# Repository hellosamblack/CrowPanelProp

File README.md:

# Communicator / Scanner Prop Firmware

Cassette-futurism communicator/scanner prop for the **CrowPanel Advance ESP32-P4 (hardware V1.0)**.
Custom ESP-IDF firmware structured as a generic *prop engine*: stable firmware whose behavior is driven
live over WiFi, so scenes/LEDs/screen text can be cued and iterated without reflashing.

Forked from `example/V1.0/idf-code/Lesson09-LVGL_Lighting_Control`.

## Architecture

| Module | Role |
|--------|------|
| `components/bsp_display`, `bsp_illuminate`, `bsp_i2c` | Display + touch + backlight bring-up (reused from Lesson09) |
| `components/bsp_io` | Discrete on/off LEDs + debounced buttons (`espressif/button`) |
| `main/prop_engine` | **The brain.** Scene state machine + 10 Hz animation task; single source of truth, fans state out to observers |
| `main/prop_net` | WiFi **AP+STA** via the onboard ESP32-C6 (`esp_hosted`); STA credentials in NVS |
| `main/prop_api` | HTTP server: operator web console, REST `/cmd`, WebSocket `/ws`, OTA `/ota` |
| `main/prop_ui` | LVGL amber-on-black retro readout — a pure view of engine state |

Inputs (physical buttons, remote commands) all funnel through `prop_engine`, which drives both the LEDs
and the screen, so they never drift out of sync.

## Scenes

`IDLE`, `SCANNING`, `SIGNAL_ACQUIRED`, `COMMS`, `ALERT` — each defines status text + an animated LED pattern.

## Build & flash

Requires **ESP-IDF ≥ 5.4.2** (v6.0.1 recommended).

**Windows:**
Use the VS Code ESP-IDF extension terminal, or `export.ps1` from your IDF install:
```powershell
idf.py set-target esp32p4
idf.py build
idf.py -p <PORT> flash monitor     # first flash over USB (UART0)
```
Or run the helper: `pwsh tools/dev.ps1 bf -Port COM7`

**Linux / Debian:**
Source your `export.sh` script to activate the environment:
```bash
. ~/.local/esp/esp-idf/export.sh
idf.py set-target esp32p4
idf.py build
idf.py -p /dev/ttyUSB0 flash monitor
```
Or run the helper: `./tools/dev.sh bf -Port /dev/ttyUSB0`

The `espressif/button`, display, and WiFi components download automatically on first build
(declared in the `idf_component.yml` files).

## Live control (no reflash)

Find the device IP from the serial log (or use the AP `PROP-COMMS` / pass `scanner99`, then `192.168.4.1`).

```bash
# REST
curl -X POST http://<ip>/cmd -d '{"cmd":"scene","value":"SCANNING"}'
curl -X POST http://<ip>/cmd -d '{"cmd":"led","name":"alert","on":true}'
curl -X POST http://<ip>/cmd -d '{"cmd":"channel","value":"CH 04 / 147.55 MHz"}'
curl      http://<ip>/state

# Operator cue board (scene buttons, live state): open http://<ip>/ in a browser
# WebSocket: ws://<ip>/ws  — send the same JSON commands, receive state broadcasts
```

Command schema: see the top of [main/include/prop_api.h](main/include/prop_api.h).

### WiFi OTA (code changes, still no USB)

**CLI (recommended)** — build + push in one command:

**Windows (PowerShell):**
```powershell
pwsh tools/dev.ps1 ota                          # defaults to comm-unit-7.local
pwsh tools/dev.ps1 ota -DeviceHost 172.17.2.167 # explicit IP fallback
```

**Linux / Debian (Bash):**
```bash
./tools/dev.sh ota                              # defaults to comm-unit-7.local
./tools/dev.sh ota -DeviceHost 172.17.2.167     # explicit IP fallback
```

**Browser** — open `http://comm-unit-7.local/`, scroll to **FIRMWARE UPDATE**, pick the
`.bin` (usually `build/communicator.bin`), click **UPLOAD**. A progress percentage appears
and the page reports "done — rebooting…" when the device is switching over.

**Raw curl** (if you prefer):

```bash
idf.py build
curl -X POST "http://<ip>/ota?token=prop-ota-2024" --data-binary @build/communicator.bin
```

**Rollback safety:** the bootloader is configured with `CONFIG_BOOTLOADER_APP_ROLLBACK_ENABLE`.
A freshly-OTA'd image boots as `PENDING_VERIFY`; `app_main` calls
`esp_ota_mark_app_valid_cancel_rollback()` after the full stack is up. If the new image
crashes before reaching that point the bootloader automatically reverts to the previous
partition on the next reset — no USB reflash required.

**Confirm the update landed:** `GET /state` includes a `"version"` field (from `git
describe`), and the web console state line shows `v<version>`.

Change `PROP_OTA_TOKEN` in [main/include/prop_api.h](main/include/prop_api.h) and the AP password in
[main/include/prop_net.h](main/include/prop_net.h) before any real deployment.

## Wiring — IMPORTANT

GPIO assignments are placeholders in [components/bsp_io/bsp_io.c](components/bsp_io/bsp_io.c). Only **GPIO48**
(the UART1-RX header pin) is confirmed broken-out and free. **Verify every other pin against the V1.0
schematic in `Eagle_SCH&PCB/1.0/` and the connector silkscreen before wiring.** Defaults used:

- LEDs: `power`=GPIO48, `signal`=GPIO47 (UART1-TX), `alert`=GPIO20
- Buttons (active-low, internal pull-up): `mode`=GPIO33 (UART3-IN), `action`=GPIO11

Buttons: `mode` cycles scenes, `action` jumps to SCANNING (edit `on_button()` in `main/main.c`).

## ESP-IDF version

**Builds clean on ESP-IDF v6.0.1** (target esp32p4). The Lesson09/17 examples were written for 5.4.2; this
project was migrated to 6.0. Changes required for 6.0 (all already applied):

- cJSON moved out of IDF core → added `espressif/cjson` dependency; `REQUIRES cjson` (not `json`).
- WiFi stack: `esp_wifi_remote` bumped to **1.x** (0.x referenced the removed `esp_interface.h`); paired with `esp_hosted` 2.12.9.
- `driver` component split → BSP components now require `esp_driver_i2c` / `esp_driver_gpio` / `esp_driver_ledc`.
- esp_lcd DPI API: `lcd_color_rgb_pixel_format_t`→`lcd_color_format_t`, `LCD_COLOR_PIXEL_FORMAT_*`→`LCD_COLOR_FMT_*`, `.pixel_format`→`.in_color_format`/`.out_color_format`, `.flags.use_dma2d` removed, RGB666 enum gone.
- Stricter warnings-as-errors: fixed a header-guard typo in `bsp_i2c.h`.
- `sdkconfig.defaults`: 16 MB flash + `CONFIG_LV_FONT_MONTSERRAT_24`.

## Status

**Compiles successfully** (`communicator.bin` builds). **Not yet flashed/run on hardware** — pending the
CH341 USB-serial driver + the board appearing on a COM port. Then work through the verification checklist
in the project plan.

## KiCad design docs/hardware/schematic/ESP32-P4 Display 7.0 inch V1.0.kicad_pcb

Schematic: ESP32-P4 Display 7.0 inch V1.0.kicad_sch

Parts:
C1, C2, C3, C10, C17, C22, C69, C86, C102: 1uF; 0603
C4: 10uF/NC; 0603
C5, C7, C9, C36, C40, C41, C43, C45, C46, C50, C60, C61, C63, C72, C73, C108, C113, C115: 100nF; C0402
C6, C8, C42, C44, C47, C48, C49, C56, C71, C107, C112, C114, C116: 10uF; C0402
C11, C15, C19, C20, C21, C35, C37, C52, C53, C54, C75, C76, C77, C80, C81, C82, C84, C144, C150, C151, C152, C155, C156, C159: 100nF; 0603
C12, C27, C28, C32: 10uF/10V+; 0603
C13, C18: 22uF; C0805
C14, C16, C38, C74, C78, C79, C83, C136, C149, C153, C157: 10uF; 0603
C23, C24, C103, C104: 47uF; 0603
C26, C31: 22pF; 0603
C29, C30: 12pF; C0402
C33, C34: 15pF; C0402
C39, C130, C132, C145: 100nF_NC; C0402
C51, C55, C57, C58, C59, C64, C65, C66: 1uF; C0402
C62: 10nF; C0402
C67, C68, C85, C105, C106, C158: 1nF; 0603
C70: 10UF; 0603
C87: 15pF; 0603
C88: 10UF_NC; 0603
C89, C101: 22pF_NC; C0402
C90, C99, C110: 10uF/25V; 0603
C91, C100, C111: 100nF/50V; 0603
C92: 22uF/16V; C0805
C93: 10nF/25V; 0603
C94: 10uF/25V; C0402
C95: 100nF/50V; C0402
C96, C97: 1uF/25V; 0603
C98, C109: 1uF/50V; 0603
C117, C118, C119, C120, C121, C122, C123, C124, C125, C126, C127, C128, C129, C131, C133, C137, C138, C139, C140, C141, C142, C146: 1uF_NC; C0402
C134, C148: 47uF_NC; 0603
C135, C147, C154: 100nF_NC; 0603
C143: 1uF_NC; 0603
D1: KT-0603RYG; LED_KT-0603RYG
D2, D007, D10: DSS34; D_SOD123FL
D003: NC/DSS34; D_SOD123FL
D4, D008, D11: 1N5817WS; D_SOD323
D005, D012, D013, D015, D017, D018: LMBR140ET1G
D14: Red; LED0603
D016: MM1W18_18V; LMSZ5233BT1G
D020: LMSZ5233BT1G_-6V; LMSZ5233BT1G
FB2, FB3, FB10, FB11: 1K/磁珠; L0603
FB4, FB5, FB13: 0R/800mA_NC; L0402
FB6: 0R/800mA; L0402
FB7, FB8, FB9, FB12: 1K/磁珠_NC; L0603
FB14: 0R/800mA_NC; R0402
FB15, FB16: 0R/800mA_NC; L0603
FB17, FB18, FB19, FB20: 0R/800mA; L0603
FB21: 0R/800mA; L0805
FPC2: FPC-6PIN-0.5MM
FPC3: AFC24-S24FIA-00; FPC-SMD_P0.50-24P_QCHF-SM-H2.0
IC1: ESP32-C6-MINI-1-N4; ESP32C6MINI1N4
IC2: ME6211C18M5G-N; SOT95P282X145-5N
IC3: ME6211C28M5G-N; SOT95P282X145-5N
IC4: ME6211C18M5G-N_NC; SOT95P282X145-5N
IC5: ES7210_NC; QFN40P400X400X80-33N
IC6: ES8311_NC; QFN40P300X300X60-21N
IC7, IC8: ME6211C33M5G-N; SOT95P282X145-5N
IC10: W25Q128JVSIQ; SOIC127P790X216-8N
J1, J16: TYPEC-3.0-16P-SMD; USB-3.0TYPEC-SMD
J2, J13: HY2.0-4P-SMT; CONNECTOR_4P-SMD-2.0
J3, J4, J6: PH2.0WT-2PIN
J5: HOLDER-MICROSD-9P; 9P-SMD-W_-RING
J7: CONN_12X22X12-SMD1; 2X12-SMD1
J8: HC-PZ200-8.7L-1X4PZ1; TEST-PIN-4-2.0MM
J9, J11: HEADER-7P-18.28X2.5; H7-2.54-18.28X2.5X5MM
J10: XH2.54-4P-SMT; XH2.54-4P-SMD
J12, J14, J15, J18: THO-M3.25MM-HOLE; THO-M3.2_5MM-HOLE
J21: C23398852_30P_0.5MM_下接_FC-05A30P11H20
K3, K4: KEY-4.5X4.5; KEY-4.5X4.5-SMD
L1, L6: 2.2μH_C5179446; 1008(2520)
L2, L5: 4.7uH_C45385206_2.4A; 1008(2520)
L4: NC; L0603
P1, P2, P3, P4, P5, P6, P7, P8, P9, P10, P11, P12, P13, P14, P15, P16, P17, P18, P19, P20, P21, P22, P23, P24, P25, P26, P27, P28, P29, P30, P31, P32, P33, P34, P35, P36, P37, P38, P39, P40, P41, P42, P43, P44, P45, P46, P47, P48, P49, P50, P51, P52, P53, P54, P55, P56, P57, P58, P59, P60, P61, P62, P63, P64, P65, P66, P67, P68, P69, P70, P71, P72, P73, P74, P75, P76, P77, P78, P79, P80, P81, P82, P83, P84, P85, P86, P87, P88: TEST_PADPAD-1.5MM; TEST_PAD-1.5MM
Q1, Q2, Q4, Q6, Q7, Q8, Q9: BSS138W_SOT323; MOS_SOT323
Q3, Q5: NCE20P45Q; PDFN3333
Q10: AO3401; PMOS_SOT23
Q11: AO3401_NC; PMOS_SOT23
R1, R5, R9, R15, R18, R27, R28, R29, R30, R53, R54, R61, R66, R67, R71, R77, R87, R91, R106, R116, R160, R180, R181: 10K; R0603
R2, R117, R139, R165: 100K; R0603
R3, R4, R17, R26, R47, R50, R96, R101: 5.1K; R0603
R6, R7, R8, R10, R13, R24, R48, R49, R55, R60, R65, R76, R103, R112, R113, R114, R115, R118, R119, R129, R149, R184, R188, R189: 0R; R0603
R11: 22.1K; R0603
R12, R19, R20, R36, R37, R38, R39, R40, R41, R42, R43, R44, R70, R80, R88, R89, R90, R92, R95, R99, R100, R102, R105, R109, R127, R162, R190, R216, R217, R332: 0R; R0402
R14, R21: NC/499K; R0603
R16, R31, R32: 2K; R0603-SP
R22, R45, R46, R51, R52, R56, R57, R58, R59, R62, R74, R78, R93, R94, R97, R98: 4.7K; R0603
R23: 0R; C0402
R25: 0R; R0603-SP
R33: 10K_NC; R0603
R35: NC/10M; R0402
R63, R64, R68, R108, R122, R123: 100K; R0402
R65_NC0, R131, R171: 10K; R0402
R69: 4.7K; R0603-SP
R72, R73: 10K_NC; R0402
R75: 4.7K_NC; R0603
R79, R147, R185: OR_NC; R0603-SP
R81, R82, R83, R84, R85, R86, R173, R175: 51K; R0603
R104, R158: 4.02K; R0402
R107, R110, R111, R124, R125, R126, R128, R130, R146, R148, R161, R170, R177: 0R_NC; R0402
R120, R121: 5.1K_NC; R0603
R132, R134: OR; R0402
R141, R142, R144, R145: OR_NC; R0402
R143: 51K; R0603-SP
R152, R153, R154, R155, R156, R157: 100R; R0402
R159: 1.1R; R0603-SP
R163: NC; R0603-SP
R164: 39k; R0603
R166: 180K; R0603
R167: 12K; R0603
R168: 1.91K; R0402
R169: 1K; R0402
R172, R174: 220R; R0603
R178, R179: 20K_NC; R0603
R182: 0R; L0805
R186: 100k; R0603
R187: 10k; R0603
R210: NC/10K; R0603
SW1: switch_6pin; SWITCH_6PIN_2P
TP1, TP2, TP3, TP4, TP5, TP6, TP7, TP8, TP9, TP10, TP11, TP12: TPTP08R; TP08R
U1: CH340K; ESOP-10-EP-150MIL
U2: TP4059-SOT23-6; SOT23-6L
U3, U13: NS4168; NS4168-ESOP-8
U4: NS4263B; SOP16
U6: MT9201; COOPER_SOT23-6
U7: ESP32-P4NRW32; IC_ESP32-P4NRW32
U8: UMH3NTN; SOP65P210X100-6N
U9, U10: MT3406_C22462728; SOT95P280X145-5N
U14: STC8H1K08-36I; TSSOP20
U16: MT3608; SOT95P280X145-6N
U176: LMA3526B381; MIC-SMD_5P-L3.5-W2.7-P1.67
Y2: 40MHZ; X322540MPB4SI
Y3: 24Mhz; 24MHZ_1631-24003-BTKEYA
Y4: 32.768K; NORDIC_NRF_XTAL_3215_N

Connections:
3V3$: C2.2, U1.10 (V3)
13: R189.2, U14.3 (MISO/P1.4)
14: R188.2, U14.4 (SCLK/P1.5)
+5V_IN: D2.+, D4.+, J10.3, P66.P$1, R46.1, R51.1
+VBUS1: D10.+, D11.+, J1.A4, J1.A9, J1.B4, J1.B9, P1.P$1
+VBUS2: D007.+, D008.+, J16.A4, J16.A9, J16.B4, J16.B9, P87.P$1
ADC_AVDD_3V3: C132.1, C133.2, FB5.2, IC5.22 (VDDA), IC5.23 (VDDM)
ADC_DVDD_3V3: C130.1, C131.2, FB4.2, IC5.6 (VDDP), IC5.7 (VDDD), R73.1
ADC_VBAT: C158.2, R164.2, R186.1, U14.13 (P3.2/ADC10)
AGND: C102.2, C103.2, C104.2, C105.1, C106.1, C134.1, C143.1, C148.1, C154.2, FB19.2, FB21.2, J4.P$3, J4.P$4, R79.2, R143.1, R185.1, U4.2, U4.7, U4.15, U13.7 (GND), U13.9 (PE)
AGND1: C72.1, C117.1, C118.1, C119.1, C120.1, C121.1, C122.1, C127.2, C128.2, C129.2, C132.2, C133.1, C137.1, C138.2, C139.2, C142.2, C145.2, C146.1, IC5.21 (GNDA), IC6.10 (AGND), R144.1, R145.2, R171.2, R182.2, U176.5_1 (5), U176.5_2 (5)
AGND3: C22.2, C23.2, C24.2, C67.1, C68.1, FB20.2, J6.P$3, J6.P$4, U3.7 (GND), U3.9 (PE)
AUDIO_CTRL: Q10.3 (D), R117.2, R139.2
AUDIO_OUT_5V: C134.2, C148.2, C154.1, FB15.2, U4.4, U4.13
AUDIO_OUT_SD: Q10.1 (G), R71.1, R147.1, U7.60 (GPIO30)
AUDIO_VDD1: C102.1, C103.1, C104.1, FB17.1, U13.6 (VDD)
AUDIO_VDD2: C22.1, C23.1, C24.1, FB18.1, U3.6 (VDD)
AUDIO_VDD_3V3: C152.2, C153.2, FB4.1, FB5.1, FB6.1, FB14.1, FB16.2, IC7.5 (VOUT)
AVDD_2V8: C82.2, C83.2, FPC3.1, FPC3.2, IC3.5 (VOUT), P83.P$1
C6_EN: C15.1, IC1.8 (EN), R77.1, U7.63 (GPIO32)
C6_IO8: IC1.22 (IO8), R87.2
C6_IO9_BOOT: IC1.23 (IO9), P36.P$1
C6_RXD0: IC1.30 (RXD0), P21.P$1
C6_TXD0: IC1.31 (TXD0), P25.P$1
C6_VDD_3V3: C11.1, C14.2, IC1.3 (3V3), P37.P$1, R76.1, R77.2, R81.1, R82.1, R83.1, R84.1, R85.1, R86.1, R87.1
CODEC_3V3: C145.1, C146.2, FB13.2, FB14.2, IC6.3 (PVDD), IC6.4 (DVDD)
CSID0_P: R153.1, U7.43 (CSI_DATAP0)
CSI_CLK_N: FPC3.19, R156.2, TP5.TP
CSI_CLK_P: FPC3.18, R157.2, TP6.TP
CSI_D0_N: FPC3.16, R152.2, TP1.TP
CSI_D0_P: FPC3.15, R153.2, TP2.TP
CSI_D1_N: FPC3.22, R154.2, TP3.TP
CSI_D1_P: FPC3.21, R155.2, TP4.TP
CSI_RESET: FPC3.8, P80.P$1, Q4.2 (S), R57.2
CSI_SCL: FPC3.4, P81.P$1, Q7.2 (S), R62.2
CSI_SDA: FPC3.5, P82.P$1, Q6.2 (S), R56.2
DA1: J5.8 (DATA1), P56.P$1, R15.1
DA2: J5.1 (DATA2), P53.P$1, R30.1
DOVDD_1V8: C77.2, C78.2, C84.2, C85.2, FPC3.9, IC2.5 (VOUT), P84.P$1, Q4.1 (G), Q6.1 (G), Q7.1 (G), R56.1, R57.1, R62.1, R67.2, Y3.4 (4_VDD)
DOWNLOAD_BOOT: R60.1, R106.2
DSI_CLK_N: J21.18, R100.1, TP11.TP
DSI_CLK_P: J21.17, R102.1, TP12.TP
DSI_DATA0_N: J21.24, R190.1, TP7.TP
DSI_DATA0_P: J21.23, R92.1, TP8.TP
DSI_DATA1_N: J21.21, R95.1, TP9.TP
DSI_DATA1_P: J21.20, R99.1, TP10.TP
DTR: R5.2, U1.4 (DTR#), U8.4 (E2)
EN_DCDC: R13.2, U7.79 (EN_DCDC)
ESP32_LDO1: C58.1, R105.2, U7.71 (VFB1/VO1)
ESP32_LDO2: C57.1, R40.2, U7.72 (VFB2/VO2)
ESP32_LDO3: C59.1, R80.2, U7.73 (VFB3/VO3)
ESP32_LDO4: C66.1, R109.2, U7.74 (VFB4/VO4)
FB_DCDC: C31.1, R14.2, R21.1, R103.1, U10.5 (FB)
FLASH_CK: IC10.6 (CLK), U7.32 (FLASH_CK)
FLASH_CS: IC10.1 (/CS), R65_NC0.1, U7.27 (FLASH_CS)
FLASH_D: IC10.5 (DI_(IO0)), U7.33 (FLASH_D)
FLASH_HOLD: IC10.7 (/HOLD_OR_/RESET_(IO3)), U7.31 (FLASH_HOLD)
FLASH_Q: IC10.2 (DO_(IO1)), U7.28 (FLASH_Q)
FLASH_WP: IC10.3 (/WP_(IO2)), U7.29 (FLASH_WP)
GND: C1.1, C2.1, C3.1, C4.1, C5.2, C6.1, C7.2, C8.1, C9.2, C10.1, C11.2, C12.2, C13.2, C14.1, C15.2, C16.1, C17.1, C18.2, C19.2, C20.1, C21.1, C27.1, C28.2, C29.2, C30.2, C32.1, C33.2, C34.1, C35.1, C36.2, C37.1, C38.1, C39.2, C40.2, C41.2, C42.1, C43.2, C44.1, C45.2, C46.2, C47.1, C48.1, C49.1, C50.2, C51.2, C52.1, C53.1, C54.1, C55.2, C56.1, C57.2, C58.2, C59.2, C60.2, C61.2, C62.2, C63.2, C64.2, C65.2, C66.2, C69.1, C70.2, C71.1, C73.2, C74.1, C75.1, C76.1, C77.1, C78.1, C79.1, C80.1, C81.1, C82.1, C83.1, C84.1, C85.1, C86.1, C87.1, C88.2, C90.2, C91.2, C92.2, C94.2, C95.2, C98.2, C99.2, C100.2, C107.1, C108.2, C109.2, C110.2, C111.2, C112.1, C113.2, C114.1, C115.2, C116.1, C130.2, C131.1, C136.1, C144.1, C149.1, C150.1, C151.1, C152.1, C153.1, C155.1, C156.1, C157.1, C158.1, C159.1, D14.-, D016.2, D018.1, D020.1, FB19.1, FB20.1, FB21.1, FPC2.4, FPC2.7, FPC2.8, FPC3.3, FPC3.6, FPC3.10, FPC3.12, FPC3.17, FPC3.20, FPC3.25, FPC3.26, IC1.1 (GND_1), IC1.2 (GND_2), IC1.11 (GND_3), IC1.14 (GND_4), IC1.36 (GND_5), IC1.37 (GND_6), IC1.38 (GND_7), IC1.39 (GND_8), IC1.40 (GND_9), IC1.41 (GND_10), IC1.42 (GND_11), IC1.43 (GND_12), IC1.44 (GND_13), IC1.45 (GND_14), IC1.46 (GND_15), IC1.47 (GND_16), IC1.48 (GND_17), IC1.49 (GND_18), IC1.50 (GND_19), IC1.51 (GND_20), IC1.52 (GND_21), IC1.53 (GND_22), IC1.54 (GND_23), IC1.55 (GND_24), IC1.56 (GND_25), IC1.57 (GND_26), IC1.58 (GND_27), IC1.59 (GND_28), IC1.60 (GND_29), IC1.61 (GND_30), IC2.2 (VSS), IC3.2 (VSS), IC4.2 (VSS), IC5.8 (GNDD), IC5.33 (EP), IC6.5 (DGND), IC6.20 (CE), IC6.21 (EP), IC7.2 (VSS), IC8.2 (VSS), IC10.4 (GND), J1.A1, J1.A12, J1.B1, J1.B12, J1.P$1, J1.P$2, J1.P$3, J1.P$4, J2.4, J2.SS1, J2.SS2, J3.P$2, J3.P$3, J3.P$4, J5.6 (VSS), J5.G1, J5.G2, J5.G3, J5.G4, J7.7, J7.8, J7.10, J7.21, J7.22, J7.23, J7.24, J8.4, J9.6, J9.6-6 (6), J10.4, J10.5 (SS1), J10.6 (SS2), J12.P$1, J13.4, J13.SS1, J13.SS2, J14.P$1, J15.P$1, J16.A1, J16.A12, J16.B1, J16.B12, J16.P$1, J16.P$2, J16.P$3, J16.P$4, J18.P$1, J21.10, J21.13, J21.16, J21.19, J21.22, J21.25, J21.31, J21.32, K3.1, K4.1, P4.P$1, P10.P$1, P12.P$1, P28.P$1, P31.P$1, P52.P$1, P60.P$1, P65.P$1, P78.P$1, P86.P$1, P88.P$1, R3.1, R4.2, R11.2, R16.1, R18.1, R21.2, R33.2, R64.1, R72.1, R96.1, R101.2, R104.1, R108.1, R123.1, R158.2, R159.1, R160.2, R163.1, R167.1, R169.1, R173.1, R175.1, R182.1, R186.2, SW1.1 (1_2B), SW1.6 (6_1B), U1.3 (GND), U1.EP, U2.2 (GND), U6.2 (2-GND), U7.105 (GND), U9.2 (GND), U10.2 (GND), U14.10 (GND), U16.2 (2_GND), Y2.2 (GND_1), Y2.4 (GND_2), Y3.2 (2_GND)
I2C1_SCL: FPC2.1, P72.P$1, Q9.2 (S), R97.2, U7.88 (GPIO46)
I2C1_SCL_3V3: IC6.1 (CCLK), J11.2, J11.2-2 (2), J13.1, P62.P$1, Q9.3 (D), R93.2, R125.1, R188.1
I2C1_SDA: FPC2.2, P71.P$1, Q8.2 (S), R98.2, U7.87 (GPIO45)
I2C1_SDA_3V3: IC6.19 (CDATA), J11.3, J11.3-3 (3), J13.2, P61.P$1, Q8.3 (D), R94.2, R124.1, R189.1
I2C2_SCL: Q7.3 (D), R59.2, U7.14 (GPIO13)
I2C2_SDA: Q6.3 (D), R22.2, U7.13 (GPIO12)
I2SOUT_LRCK1: R149.2, U13.2 (LRCLK)
I2SOUT_LRCK2: P35.P$1, R114.2, U3.2 (LRCLK)
I2SOUT_SCLK1: R129.2, U13.3 (BCLK)
I2SOUT_SCLK2: P34.P$1, R113.2, U3.3 (BCLK)
I2SOUT_SD1: R112.2, U13.4 (SDATA)
I2SOUT_SD2: P33.P$1, R115.2, U3.4 (SDATA)
I2S_LRCK: R114.1, R130.1, R149.1, U7.23 (GPIO21)
I2S_LRCK_N: IC5.10 (LRCK), IC6.8 (LRCK), R130.2
I2S_MCLK: R126.1, R127.1, U7.52 (GPIO24)
I2S_MCLK_N: IC5.5 (MCLK), IC6.2 (MCLK), R126.2
I2S_SCLK: R113.1, R128.1, R129.1, U7.24 (GPIO22)
I2S_SCLK_N: IC5.9 (SCLK), IC6.6 (SCLK/DMIC_SCL), R128.2
I2S_SDIN1_N: IC5.11 (SDOUT1/TDMOUT)
I2S_SDIN2: R161.1, R162.1, U7.55 (GPIO26)
I2S_SDIN2_N: IC5.12 (SDOUT2/TDMIN), R161.2
I2S_SDOUT: R111.1, R112.1, R115.1, U7.25 (GPIO23)
I2S_SDOUT_N: IC6.9 (DSDIN), R111.2
INLN: C147.1, R148.2
INLN1: R179.1, U4.6
INRN: C135.1, R146.2
INRN1: R178.1, U4.11
INT_TP: FPC2.3, P70.P$1, R75.2, U7.83 (GPIO42)
IO8: R217.1, U7.8 (GPIO8)
IO9_W: J11.5, J11.5-5 (5), P23.P$1, U7.10 (GPIO9)
IO10_W_BUSY: J11.6, J11.6-6 (6), P22.P$1, U7.11 (GPIO10)
IO11_CSI_RESET: Q4.3 (D), R58.2, U7.12 (GPIO11)
LCD_AVDD_9V6: C92.1, C93.1, D005.2, D013.1, J21.9, P19.P$1, R166.2, R168.2
LCD_BK_EN: R160.1, U6.4 (4-EN), U7.61 (GPIO31)
LCD_BK_POWER: Q11.1 (G), R180.1, U7.58 (GPIO29)
LCD_BK_VDD: C13.1, C17.2, L5.1, Q11.3 (D), R184.2, U6.6 (6-VIN)
LCD_RESET: J21.27, P73.P$1, R69.2, U7.82 (GPIO41)
LCD_VCOM_3V3: C94.1, C95.1, J21.30, P20.P$1, R168.1, R169.2
LCD_VDD: C37.2, C38.2, C52.2, C53.2, FPC2.5, IC4.5 (VOUT), J21.28, J21.29, P69.P$1, R63.2, R65.1, R68.2, R122.2
LCD_VGH_18V: C99.1, C100.1, D016.1, J21.3, P18.P$1, R172.1, R173.2
LCD_VGL_-6V: C110.1, C111.1, D020.2, J21.4, P77.P$1, R174.1, R175.2
LED+: C18.1, C19.1, D003.-, D012.1, P63.P$1, R25.1, U6.5 (5-OV)
LED-: J21.7, J21.8, P64.P$1, R159.2, R163.2, U6.3 (3-FB)
MIC1N: C89.2
MIC1P: C101.2
MIC2N: C125.2, R141.2
MIC2P: C126.2, R142.2
MIC2_1: R132.2, R142.1, U176.1
MIC2_2: R131.1, R141.1, R145.1, R171.1, U176.2
MIC2_3: R134.1, R144.2, U176.3
MIC2_VDD_3V3: C72.2, FB6.2, U176.4
MIC3N: C124.1, R170.2
MIC3P: C123.1, R177.2
MIC_L/R: R131.2, U7.22 (GPIO20)
MIC_MCLK: P27.P$1, R127.2, R134.2
MIC_SD2: P30.P$1, R132.1, R162.2
unnamed: R1.1, U9.1 (EN)
unnamed: L1.1, U9.3 (SW)
unnamed: FB7.1, U4.12
unnamed: FB10.1, U13.8 (VOP)
unnamed: R6.1, U1.1 (UD+)
unnamed: R7.1, U1.2 (UD-)
unnamed: R5.1, U8.2 (B1)
unnamed: R9.1, U8.5 (B2)
unnamed: J1.B5, R3.2
unnamed: R8.2, U1.9 (RXD)
unnamed: R10.2, U1.8 (TXD)
unnamed: R16.2, U2.6 (PRO)
unnamed: C26.1, R2.2, R11.1, U9.5 (FB)
unnamed: L6.1, U10.3 (SW)
unnamed: C151.2, IC7.3 (CE), R181.1
unnamed: R13.1, R210.2, U10.1 (EN)
unnamed: C143.2, U4.10
unnamed: R185.2, U4.8
unnamed: D1.3, R31.1, R121.1
unnamed: D1.4, R32.1, R120.1
unnamed: D14.+, R26.1
unnamed: J21.1, J21.2, R25.2
unnamed: J9.1, J9.1-1 (1), R49.1
unnamed: J11.1, J11.1-1 (1), R48.1
unnamed: FB8.1, U4.14
unnamed: Q5.4 (4_G), R78.1, SW1.2 (2_COM2), SW1.5 (5_COM1)
unnamed: J1.A5, R4.1
unnamed: R79.1, U4.16
unnamed: C28.1, R24.1, R210.1, U10.4 (VIN)
unnamed: R190.2, U7.40 (DSI_DATAN0)
unnamed: R92.2, U7.39 (DSI_DATAP0)
unnamed: C30.1, R35.1, U7.1 (GPIO1), Y4.2
unnamed: C29.1, R35.2, U7.104 (GPIO0), Y4.1
unnamed: R95.2, U7.36 (DSI_DATAN1)
unnamed: R99.2, U7.35 (DSI_DATAP1)
unnamed: R100.2, U7.37 (DSI_CLKN)
unnamed: C147.2, R179.2
unnamed: R102.2, U7.38 (DSI_CLKP)
unnamed: R103.2, U7.78 (FB_DCDC)
unnamed: R104.2, U7.34 (DSI_REXT)
unnamed: C21.2, IC4.3 (CE), R53.1
unnamed: C135.2, R178.2
unnamed: FB2.1, U3.8 (VOP)
unnamed: FB11.1, U13.5 (VON)
unnamed: FB3.1, U3.5 (VON)
unnamed: R117.1, U3.1 (CTRL)
unnamed: R118.2, U14.12 (P3.1/ADC9)
unnamed: R119.2, U14.11 (P3.0/ADC8)
unnamed: R139.1, R143.2, U13.1 (CTRL)
unnamed: IC5.3 (CDATA), R124.2
unnamed: IC5.4 (CCLK), R125.2
unnamed: FB9.1, U4.3
unnamed: C155.2, IC8.3 (CE), R116.1
unnamed: C159.2, R187.2, U14.7 (NRST/PWM6/P5.4)
unnamed: FB12.1, U4.5
unnamed: C124.2, IC5.32 (MIC3N)
unnamed: C89.1, IC5.15 (MIC1N)
unnamed: C101.1, IC5.16 (MIC1P)
unnamed: R332.1, U7.7 (GPIO7)
unnamed: R216.1, U7.6 (GPIO6)
unnamed: R158.1, U7.48 (CSI_REXT)
unnamed: R157.1, U7.44 (CSI_CLKP)
unnamed: R156.1, U7.45 (CSI_CLKN)
unnamed: R155.1, U7.47 (CSI_DATAP1)
unnamed: R154.1, U7.46 (CSI_DATAN1)
unnamed: R152.1, U7.42 (CSI_DATAN0)
unnamed: J16.B5, R96.2
unnamed: J16.A5, R101.1
unnamed: C123.2, IC5.31 (MIC3P)
unnamed: C122.2, IC5.30 (REFQ34)
unnamed: C121.2, IC5.29 (REFP34)
unnamed: C76.2, IC2.3 (CE), R61.1
unnamed: C81.2, IC3.3 (CE), R66.1
unnamed: C86.2, R67.1, Y3.1 (1_EN)
unnamed: C120.2, IC5.28 (MIC4P)
unnamed: C119.2, IC5.27 (MIC4N)
unnamed: C118.2, IC5.26 (MICBIAS34)
unnamed: C117.2, IC5.25 (REFQM)
unnamed: C129.1, IC5.24 (MICBIAS12)
unnamed: C125.1, IC5.20 (MIC2N)
unnamed: C126.1, IC5.19 (MIC2P)
unnamed: C127.1, IC5.18 (REFQ12)
unnamed: C128.1, IC5.17 (REFP12)
unnamed: R147.2, U4.1
unnamed: C97.2, D017.1, D018.2
unnamed: IC5.1 (AD0), R73.2
unnamed: IC5.2 (AD1), R72.2
unnamed: C139.1, IC6.14 (DACVREF)
unnamed: C137.2, IC6.16 (VMID)
unnamed: C138.1, IC6.15 (ADCVREF)
unnamed: C140.1, IC6.13 (OUTN)
unnamed: C141.1, IC6.12 (OUTP)
unnamed: C142.1, FB13.1, IC6.11 (AVDD)
unnamed: D003.+, D012.2, L5.2, U6.1 (1-SW)
unnamed: C96.1, C97.1, D013.2, L2.2, U16.1 (1_SW)
unnamed: R165.2, U16.4 (4_EN)
unnamed: C96.2, D005.1, D015.2
unnamed: C98.1, D015.1, R172.2
unnamed: C140.2, R146.1, R170.1
unnamed: C141.2, R148.1, R177.1
P4_IO2: J7.9, P40.P$1, U7.2 (GPIO2)
P4_IO3: J7.11, P41.P$1, U7.3 (GPIO3)
P4_IO4: J7.13, P42.P$1, U7.4 (GPIO4)
P4_IO5: J7.15, P43.P$1, U7.5 (GPIO5)
P4_IO25: J7.17, P85.P$1, U7.53 (GPIO25)
P4_IO27: J7.19, P44.P$1, U7.56 (GPIO27)
P4_IO28: J7.20, P49.P$1, U7.57 (GPIO28)
P4_IO35: R55.2, U7.66 (GPIO35)
P4_IO36: R60.2, U7.68 (GPIO36)
P4_IO39: R90.2, U7.80 (GPIO39)
P4_IO43: R88.2, U7.84 (GPIO43)
P4_IO44: R89.2, U7.86 (GPIO44)
P4_IO49: J7.18, P48.P$1, U7.92 (GPIO49)
P4_IO50: J7.16, P47.P$1, U7.93 (GPIO50)
P4_IO51: J7.14, P46.P$1, U7.94 (GPIO51)
P4_IO52: J7.12, P45.P$1, U7.95 (GPIO52)
P4_RST_EN: C35.2, K4.2, R54.2, U7.103 (CHIP_PU), U8.6 (C1)
P4_RXD2: P59.P$1, R48.2, U7.98 (GPIO54)
P4_TXD2: P58.P$1, R49.2, U7.97 (GPIO53)
P4_VBAT: C9.1, C42.2, R20.1, U7.102 (VBAT)
POWER_CHRG: R50.1, R120.2, U2.1 (CHG), U14.14 (P3.3/ADC11)
POWER_DONE: R47.1, R121.2, U2.5 (STD), U14.15 (P3.4/ADC11)
POWER_G_LED: R31.2, U14.17 (P3.6/ADC14)
POWER_R_LED: R32.2, U14.16 (P3.5/ADC13)
RESET_TP: FPC2.6, P29.P$1, R74.2, U7.81 (GPIO40)
RTS: R9.2, U1.6 (RTS#), U8.1 (E1)
RXD0: R10.1, U7.70 (GPIO38)
RXD1: J2.1, P39.P$1, U7.90 (GPIO48)
RXD3: Q2.2 (S), R45.2, U7.64 (GPIO33)
SD1_CMD: J5.3 (DI), P8.P$1, R28.1, R89.1
SD1_D0: J5.7 (DO), P6.P$1, R27.1, R90.1
SD1_SCK: J5.5 (SCLK), P7.P$1, R88.1
SD2_CLK: IC1.25 (IO19), R82.2, U7.19 (GPIO18)
SD2_CMD: IC1.24 (IO18), R81.2, U7.20 (GPIO19)
SD2_D0: IC1.26 (IO20), R83.2, U7.15 (GPIO14)
SD2_D1: IC1.27 (IO21), R84.2, U7.16 (GPIO15)
SD2_D2: IC1.28 (IO22), R85.2, U7.17 (GPIO16)
SD2_D3: IC1.29 (IO23), R86.2, U7.18 (GPIO17)
SDCS: J5.2 (CS), P57.P$1, R29.1, R33.1
SHLR: J21.6, P75.P$1, R122.1, R123.2
SPI2_MISO: J9.3, J9.3-3 (3), P15.P$1, R332.2
SPI2_MOSI: J9.4, J9.4-4 (4), P14.P$1, R216.2
SPI2_SCK: J9.2, J9.2-2 (2), P16.P$1, R217.2
SPI_BOOT: C54.2, K3.2, R55.1, R91.2, U8.3 (C2)
STBYB: J21.26, P74.P$1, R63.1, R64.2
STC8_RXD: J8.2, R119.1
STC8_TXD: J8.1, R118.1
STC8_VDD_3V3: C69.2, C156.2, C157.2, IC8.5 (VOUT), J8.3, R187.1, U14.8 (VCC), U14.9 (VREF)
TXD0: R8.1, U7.69 (GPIO37)
TXD1: J2.2, P38.P$1, U7.89 (GPIO47)
TXD3: Q1.2 (S), R52.2, U7.65 (GPIO34)
UART_IN_RXD3: J10.2, P67.P$1, Q2.3 (D), R46.2
UART_IN_TXD3: J10.1, P68.P$1, Q1.3 (D), R51.2
UPDN: J21.5, P76.P$1, R68.1, R108.2
USB1_D+: J1.A6, J1.B6, P2.P$1, R6.2
USB1_D-: J1.A7, J1.B7, P3.P$1, R7.2
USB2_D+: J16.A6, J16.B6, U7.50 (DP)
USB2_D-: J16.A7, J16.B7, U7.49 (DM)
VBAT: C4.2, J3.P$1, P9.P$1, Q3.5 (5_D), Q3.6 (6_D), Q3.7 (7_D), Q3.8 (8_D), Q3.9 (9_D), R17.1, R164.1, U2.3 (BAT)
VCC5V: C136.2, C144.2, D1.1, D1.2, D2.-, D007.-, D10.-, IC8.1 (VIN), P11.P$1, Q3.1 (1_S), Q3.2 (2_S), Q3.3 (3_S), Q5.1 (1_S), Q5.2 (2_S), Q5.3 (3_S), R78.2, R116.2
VCC5V_IN: C3.2, D4.-, D008.-, D11.-, Q3.4 (4_G), R17.2, R18.2, R47.2, R50.2, U2.4 (VCC)
VCCA: C43.1, C47.2, R23.1, U7.51 (VCCA)
VDD5V: C12.1, C90.1, C91.1, C149.2, C150.2, FB15.1, FB17.2, FB18.2, IC7.1 (VIN), J7.2, J7.4, J7.6, L2.1, L4.2, P5.P$1, P51.P$1, Q5.5 (5_D), Q5.6 (6_D), Q5.7 (7_D), Q5.8 (8_D), Q5.9 (9_D), Q11.2 (S), R1.2, R24.2, R26.2, R165.1, R180.2, R181.2, R184.1, U9.4 (VIN), U16.5 (5_IN)
VDD5V_W: C88.1, J9.7, J9.7-7 (7), L4.1
VDDA: C7.1, C8.2, R19.1, U7.101 (VDDA)
VDDPST: C36.1, C55.1, R40.1, R110.1, U7.59 (VDDPST), U7.67 (VDDPST)
VDDPST_1: C73.1, C107.2, R36.1, U7.9 (VDDPST_1)
VDDPST_2: C41.1, C44.2, R37.1, U7.21 (VDDPST_2)
VDDPST_3: C45.1, C49.2, R38.1, U7.30 (VDDPST_3)
VDDPST_4: C50.1, C56.2, R39.1, U7.62 (VDDPST_4)
VDDPST_5: C60.1, C65.1, Q8.1 (G), Q9.1 (G), R69.1, R74.1, R75.1, R97.1, R98.1, R109.1, U7.85 (VDDPST_5)
VDDPST_6: C61.1, C71.2, R41.1, U7.96 (VDDPST_6)
VDDPST_DCDC: C5.1, C6.2, R12.1, U7.77 (VDDPST_DCDC)
VDDPST_LDO: C46.1, C48.2, R70.1, U7.75 (VDDPST_LDO)
VDD_1V2: C31.2, C32.2, L6.2, P24.P$1, R14.1, R42.2, R43.2, R44.2
VDD_3V3: C1.2, C10.2, C16.2, C20.2, C26.2, C27.2, C70.1, C74.2, C75.2, C79.2, C80.2, FB16.1, IC2.1 (VIN), IC3.1 (VIN), IC4.1 (VIN), J2.3, J5.4 (VDD), J7.1, J7.3, J7.5, J9.5, J9.5-5 (5), J13.3, L1.2, P13.P$1, P17.P$1, P50.P$1, Q1.1 (G), Q2.1 (G), Q10.2 (S), R2.1, R12.2, R15.2, R19.2, R20.2, R22.1, R23.2, R27.2, R28.2, R29.2, R30.2, R36.2, R37.2, R38.2, R39.2, R41.2, R45.1, R52.1, R53.2, R54.1, R58.1, R59.1, R61.2, R65.2, R66.2, R70.2, R71.2, R76.2, R91.1, R93.1, R94.1, R106.1, R107.2, R110.2, U1.7 (VCC)
VDD_FLASH: C39.1, C40.1, C51.1, IC10.8 (VCC), R65_NC0.2, R105.1, R107.1
VDD_HP_0: C108.1, C112.2, R42.1, U7.26 (VDD_HP_0)
VDD_HP_2: C113.1, C114.2, R43.1, U7.76 (VDD_HP_2)
VDD_HP_3: C115.1, C116.2, R44.1, U7.91 (VDD_HP_3)
VDD_MIPI_DPHY: C62.1, C63.1, C64.1, R80.1, U7.41 (VDD_MIPI_DPHY)
VOLN: C106.2, FB11.2, FB12.2, J4.P$2, P55.P$1
VOLP: C105.2, FB9.2, FB10.2, J4.P$1, P54.P$1
VORN: C68.2, FB3.2, FB7.2, J6.P$2, P32.P$1
VORP: C67.2, FB2.2, FB8.2, J6.P$1, P26.P$1
XTAL_N: C34.2, U7.99 (XTAL_N), Y2.3 (CRYSTAL_2)
XTAL_P: C33.1, U7.100 (XTAL_P), Y2.1 (CRYSTAL_1)
XVCLK: C87.2, FPC3.11, P79.P$1, Y3.3 (3_OUT)

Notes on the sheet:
7.0 inch IPS interface
I2C_OUT
Audio_ADC/DAC
Battery and control
ESP32-P4_POWER
UART0_OUT
ESP32-P4
Simulated microphone U176 usage LMA3526B381，Welding R142,R141,R145,R144, NC:R132,R134,R131,R171 The digital microphone U176 usage LMD3526B381，Welding R132,R134,R131,R171, NC:R142,R141,R145,R144
USB TO UART
ESP32-C6
HIG: SPI Boot
UART_5V_IN
LOW: Download Boot
SD card
LDO:5V to 3V3(AUDIO POWER)
Power_LED
Power SW
UART & I2C & GPIO extensions
USB interface
I led=200mV/1.1=182mA
CSI_Interface
RESET
Charge indicator control
LOW: ESP32-P4 Off
DC-DC:5V to 1V2
LCD_POWER
DSI_LED Driver
BOOT
PDM MIC
DC-DC:5V to 3V3
Wireless module
Audio_OUT
HIG: ESP32-P4 Enable

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
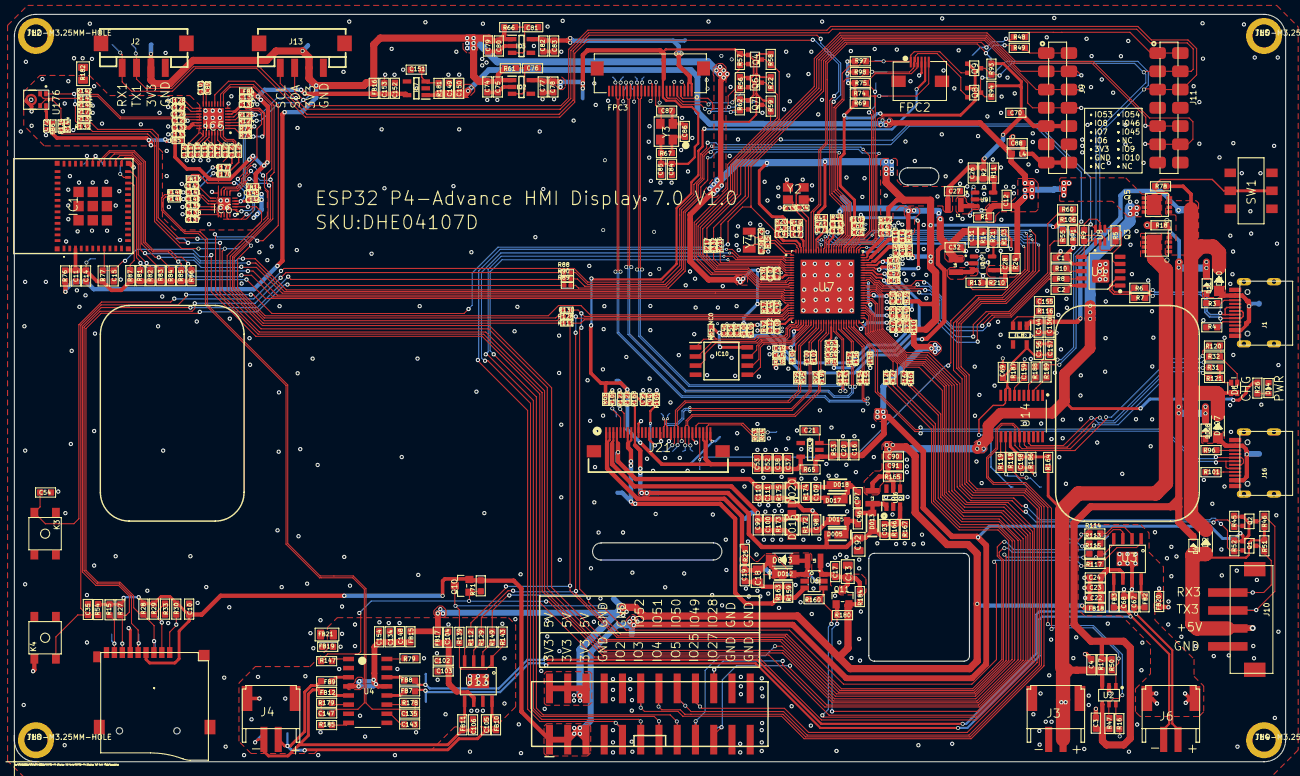
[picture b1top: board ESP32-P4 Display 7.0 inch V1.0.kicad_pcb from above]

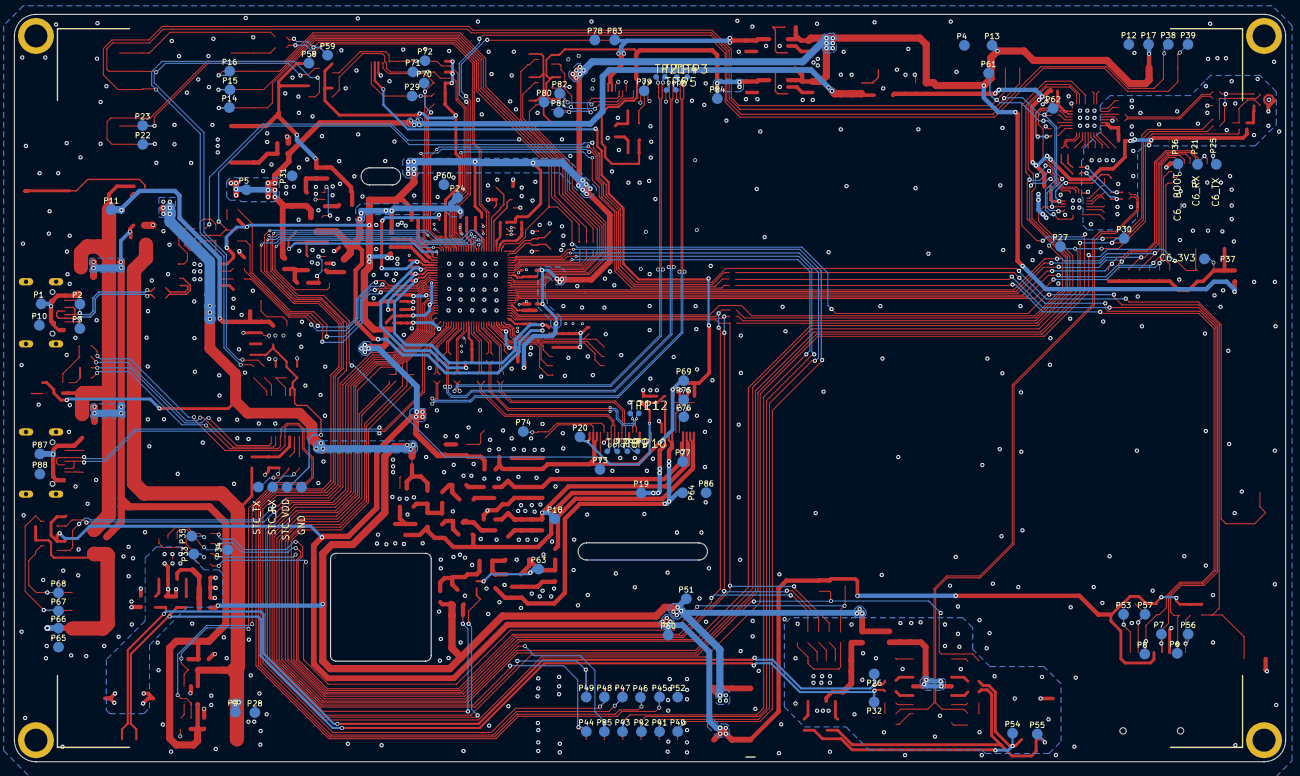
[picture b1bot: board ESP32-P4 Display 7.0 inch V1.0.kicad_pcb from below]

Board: 2 copper layers, 176.9 x 104.0 mm, 544 parts (101 on the bottom side), 303 nets.

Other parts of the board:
U$113: P4-LCD-7.0-BK3

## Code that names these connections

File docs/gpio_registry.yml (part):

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
gpios:

  # ── LP-domain GPIOs (GPIO0–15) ─────────────────────────────────────────────
  # These survive deep-sleep when powered by VDD_LP. All support capacitive touch
  # sensing and are in the fully-connected GPIO matrix for UART/SPI/I2C/PWM/etc.

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    connector_pin: J11/5
    file: CLAUDE.md
    caps: [lp_gpio, touch_ch8, spi2_ck, gpio_matrix]
    notes: J11 IO9_W header pin. Free when no radio. LP-capable.

  - gpio: 10
    status: radio           # bsp_aio "IO10 COMM" — radio NSS/CS when radio fitted
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    connector_pin: J11/6
    file: components/bsp_aio/bsp_aio.c:33
    caps: [lp_gpio, touch_ch9, spi2_q, gpio_matrix]
    notes: J11 IO10_W_BUSY header pin. Free when no radio. LP-capable.

  - gpio: 11
    status: reserved        # CSI_RESET — hardwired to the camera connector
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    caps: [lp_gpio, touch_ch14, gpio_matrix]
    notes: CONFIG_ESP_HOSTED_SDIO_PIN_D1. Do not reassign.

  # ── HP-domain GPIOs (GPIO16+) ───────────────────────────────────────────────
  # No LP/deep-sleep capability. No capacitive touch. Full GPIO matrix.

  - gpio: 18
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    file: ~
    caps: [gpio_matrix]
    notes: >
      Previously SEN0395 UART1 TX; SEN0395 moved to J10 (GPIO34/33). Now free.

  - gpio: 26
    status: claimed
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    file: ~
    caps: [gpio_matrix]
    notes: >
      Previously SEN0395 UART1 RX; SEN0395 moved to J10 (GPIO34/33). Now free.

  - gpio: 28
    status: claimed         # BTN_MODE reassigned here from GPIO33
    function: Button Mode (BTN_MODE, bsp_io)
    connector_pin: J7/20
    file: components/bsp_io/bsp_io.c
    caps: [gpio_matrix]
    notes: >
      Reassigned from GPIO33 to free UART3 RX. Removed from bsp_aio s_pins[].

  - gpio: 30
    status: claimed
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    file: main/prop_aux_radar.c
    caps: [gpio_matrix, uart3_rx, adc_capable]
    notes: >
      J10 UART1 RX (routed via GPIO matrix). SEN0395 moved here from J7/GPIO27.
      BTN_MODE previously on GPIO33; moved to GPIO28.

  - gpio: 34
    status: claimed         # SEN0395 UART1 TX — prop_aux_radar.c
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    file: main/prop_aux_radar.c
    caps: [gpio_matrix, uart3_tx, strapping_jtag_sel]
    notes: >
      J10 UART1 TX (routed via GPIO matrix). SEN0395 moved here from J7/GPIO25.
      Strapping pin: JTAG_SEL sampled at boot; pull-up holds high (JTAG
      disabled) — safe for normal operation.

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  # driver at 1.8V (ESP32-P4 side) with BSS138 level shifters to 3.3V on headers.
  # The 3.3V side is broken out on J11 pins 2-3 and J13 pins 1-2.

  - gpio: i2c1_scl_3v3     # not a GPIO number — a shared bus endpoint
    status: pseudo_available
    function: I2C1 SCL (touchscreen bus, 3.3V side)
    connector_pin: J11/2, J13/1
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      no address conflict with GT911. Uses i2c_dev_register(0x68) on the
      existing i2c_bus_handle.

  - gpio: i2c1_sda_3v3
    status: pseudo_available
    function: I2C1 SDA (touchscreen bus, 3.3V side)
    connector_pin: J11/3, J13/2
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
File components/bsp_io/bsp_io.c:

/* bsp_io — discrete LED outputs + debounced buttons. See bsp_io.h. */
#include "bsp_io.h"
#include "esp_log.h"
#include "driver/gpio.h"
#include "iot_button.h"
#include "button_gpio.h"

/* ---- Hardware tables -----------------------------------------------------
 * Edit these to match your wiring. Indices MUST match the enums in bsp_io.h.
 * gpio = -1 marks an unassigned slot: state is still tracked but no pin is
 * configured or driven. GPIO47/48 belong to the Seeed MR24HPC1 UART3 link
 * (prop_aux_radar) and GPIO11 is hardwired to CSI_RESET on the camera
 * connector — none of them may be driven as IO here.
 */
static const struct {
    int gpio;
    const char *name;
} led_table[LED_COUNT] = {
    [LED_POWER]  = { -1, "power"  },  /* GPIO48 = Seeed radar UART3 RX — unassigned */
    [LED_SIGNAL] = { -1, "signal" },  /* GPIO47 = Seeed radar UART3 TX — unassigned */
    [LED_ALERT]  = { 20, "alert"  },  /* candidate free pin; verify before wiring  */
};

static const struct {
    int gpio;
    const char *name;
} button_table[BTN_COUNT] = {
    [BTN_MODE]   = { 28, "mode"   },  /* reassigned to J7/B20; GPIO33 freed for Seeed UART3 */
    [BTN_ACTION] = { -1, "action" },  /* GPIO11 = CSI_RESET (camera connector) — unassigned */
};

/* ---- State -------------------------------------------------------------- */
static bool s_led_state[LED_COUNT];
static bsp_io_button_cb_t s_btn_cb;
static void *s_btn_ctx;
static button_handle_t s_btn_handles[BTN_COUNT];

/* Maps an iot_button event to our event + button index passed via usr_data. */
static void button_event_handler(void *arg, void *usr_data)
{
    intptr_t packed = (intptr_t)usr_data;
    prop_button_t button = (prop_button_t)(packed & 0xFF);
    prop_button_event_t event = (prop_button_event_t)((packed >> 8) & 0xFF);
    if (s_btn_cb) {
        s_btn_cb(button, event, s_btn_ctx);
    }
}

const char *bsp_io_led_name(prop_led_t led)
{
    return (led < LED_COUNT) ? led_table[led].name : "?";
}

esp_err_t bsp_io_led_set(prop_led_t led, bool on)
{
    if (led >= LED_COUNT) {
        return ESP_ERR_INVALID_ARG;
    }
    s_led_state[led] = on;
    if (led_table[led].gpio < 0) {
        return ESP_OK;   /* unassigned slot: track state only, no pin to drive */
    }
    return gpio_set_level(led_table[led].gpio, on ? 1 : 0);
}

esp_err_t bsp_io_led_set_mask(uint32_t mask)
{
    esp_err_t err = ESP_OK;
    for (int i = 0; i < LED_COUNT; i++) {
        esp_err_t e = bsp_io_led_set((prop_led_t)i, (mask >> i) & 0x1);
        if (e != ESP_OK) {
            err = e;
        }
    }
    return err;
}

bool bsp_io_led_get(prop_led_t led)
{
    return (led < LED_COUNT) ? s_led_state[led] : false;
}

static esp_err_t led_init(void)
{
    uint64_t pin_mask = 0;
    for (int i = 0; i < LED_COUNT; i++) {
        if (led_table[i].gpio >= 0) {
            pin_mask |= (1ULL << led_table[i].gpio);
        }
    }
    if (pin_mask == 0) {
        return bsp_io_led_set_mask(0);   /* nothing wired; just clear cached state */
    }
    const gpio_config_t cfg = {
        .pin_bit_mask = pin_mask,
        .mode = GPIO_MODE_OUTPUT,
        .pull_up_en = false,
        .pull_down_en = false,
        .intr_type = GPIO_INTR_DISABLE,
    };
    esp_err_t err = gpio_config(&cfg);
    if (err != ESP_OK) {
        return err;
    }
    return bsp_io_led_set_mask(0);  /* all off */
}

/* Registers one iot_button with PRESS_DOWN, LONG_PRESS_START, PRESS_UP callbacks. */
static esp_err_t register_button(prop_button_t idx)
{
    if (button_table[idx].gpio < 0) {
        return ESP_OK;   /* unassigned slot: nothing to register */
    }
    const button_config_t btn_cfg = { 0 };
    const button_gpio_config_t gpio_cfg = {
        .gpio_num = button_table[idx].gpio,
        .active_level = 0,          /* active-low with pull-up */
        .enable_power_save = false,
        .disable_pull = false,
    };
    esp_err_t err = iot_button_new_gpio_device(&btn_cfg, &gpio_cfg, &s_btn_handles[idx]);
    if (err != ESP_OK) {
        ESP_LOGE(IO_TAG, "button '%s' (gpio %d) create failed: %s",
                 button_table[idx].name, button_table[idx].gpio, esp_err_to_name(err));
        return err;
    }

    /* Pack (event<<8 | button index) into the user_data pointer. */
    intptr_t press   = (intptr_t)((BTN_EVENT_PRESS      << 8) | idx);
    intptr_t lpress  = (intptr_t)((BTN_EVENT_LONG_PRESS << 8) | idx);
    intptr_t release = (intptr_t)((BTN_EVENT_RELEASE    << 8) | idx);
    iot_button_register_cb(s_btn_handles[idx], BUTTON_PRESS_DOWN,      NULL, button_event_handler, (void *)press);
    iot_button_register_cb(s_btn_handles[idx], BUTTON_LONG_PRESS_START, NULL, button_event_handler, (void *)lpress);
    iot_button_register_cb(s_btn_handles[idx], BUTTON_PRESS_UP,         NULL, button_event_handler, (void *)release);
    return ESP_OK;
}

esp_err_t bsp_io_init(bsp_io_button_cb_t cb, void *user_ctx)
{
    s_btn_cb = cb;
    s_btn_ctx = user_ctx;

    esp_err_t err = led_init();
    if (err != ESP_OK) {
        ESP_LOGE(IO_TAG, "LED init failed: %s", esp_err_to_name(err));
        return err;
    }
    ESP_LOGI(IO_TAG, "%d LEDs initialized", LED_COUNT);

    if (cb) {
        for (int i = 0; i < BTN_COUNT; i++) {
            esp_err_t e = register_button((prop_button_t)i);
            if (e != ESP_OK) {
                return e;  /* surface wiring/pin errors early */
            }
        }
        ESP_LOGI(IO_TAG, "%d buttons registered", BTN_COUNT);
    }
    return ESP_OK;
}

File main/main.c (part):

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                   esp_err_to_name(audio_err));
    }

    /* LD2450 24 GHz multi-target radar on UART2 (GPIO53/54). NON-fatal. */
    prop_bootlog_mark(BOOT_STAGE_MOTION);
    esp_err_t motion_err = prop_motion_init();
    if (motion_err != ESP_OK) {
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                   esp_err_to_name(motion_err));
    }

    /* MPU-6500 IMU with DMP on the shared I2C_NUM_0 bus (GPIO45/46, addr 0x68).
     * NON-fatal: absent if the module is not wired; VITALS/SCANNER show "-- °". */
    prop_bootlog_mark(BOOT_STAGE_IMU);
    esp_err_t imu_err = prop_imu_init();
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                   esp_err_to_name(track_err));
    }

    /* Seeed 24 GHz (UART3, GPIO47/48, J2) + SEN0395 (UART1, GPIO34/33, J10). NON-fatal. */
    prop_bootlog_mark(BOOT_STAGE_AUX_RADAR);
    esp_err_t aux_err = prop_aux_radar_init();
    if (aux_err != ESP_OK) {
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
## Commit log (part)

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2026-06-19 Initial build
2026-06-19 Add development tools and screenshot functionality for communicator firmware
    - Introduced a PowerShell script (dev.ps1) to streamline build, flash, and monitor actions for the communicator firmware, ensuring UTF-8 encoding to prevent crashes.
    - Added a Python script (screenshot.py) to fetch and save live UI screenshots from the device's /screenshot endpoint, converting RGB565 data to PNG format without external libraries.
    - Included two PNG images (main_screen.png and wifi_page.png) for use in the communicator tools.
2026-06-19 Refactor code structure for improved readability and maintainability
2026-06-21 Antirollback
2026-06-21 Initialize LVGLPro
2026-06-21 add fonts to lvgl pro
2026-06-21 Enhance prop_mic functionality with ADC support and improve UI spectrum display
2026-06-21 Add audio feedback and initialize all screens
2026-06-21 Wire in navigation
2026-06-22 Add RTOS & Memory Reference documentation for ESP-IDF 6.x / ESP32-P4
2026-06-22 Add prop_coproc module for custom-RPC link to C6 and update main application
2026-06-25 Add continuous adaptive auto-calibration for CSI motion detection
    - Introduced `prop_calib` module for continuous adaptive threshold calibration based on live movement metrics.
    - Implemented functions for initialization, resetting the learning window, and managing adaptive control.
    - Added status reporting structure to provide real-time feedback on calibration status.
    Create canonical runtime-configurable CSI settings list
    - Added `prop_csi_cfg_list` to define runtime-configurable settings for CSI and ESPectre.
    - Utilized X-macro for easy addition and management of configuration parameters.
2026-06-26 Wire prop_motion/imu/aux_radar inits in main.c, replace prop_radar_init
2026-06-29 feat(pulse): implement wavy Halo pulse rendering with ARGB8888 canvas
2026-06-30 Add datasheets and schematics
